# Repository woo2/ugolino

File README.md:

# The Ugolino
An Arduino compaible board based on the ATMEGA328PB that uses the secondary SPI
bus provided by the 328 to interface with 256k of SRAM. There are two aditional
AVRs on borad, both are ATTINY85 microcontrollers. The 85s share the SRAM with
the 328. The 85s' each have four GPIO pins broken out. In order to implement
this functionality, bus switches were used to multiplex the SPI bus and GPIO of
each 85.

An ATMEGA16u2 was used as a USB to serial tranceiver. Right now, support for the
328pb is limited, a patch for the pb is needed for avrdude, and the Arduino IDE
requires an extra board to be installed.

## Known Issues
* ~MISO and MOSI on the Tinys are labeled with respect to the host, where the
tiny is a slave.~(fixed)
* ~SS_328 is not connected to the SS line of the RAM.~ (fixed)
* The PCB does not yet reflect the changes marked fixed.
corrected.

## How to put code on the 328PB

1. Flash the U2:

  Running parts 1 and 2 together did not work for me. It could be that the fuses need to be written before the flash can be programmed properly. Use the same command up to the ```-U``` in part 1 for part 2.
  1. ```sudo avrdude -p m16u2 -c usbtiny -U lfuse:w:0xFF:m -U hfuse:w:0xD9:m -U efuse:w:0xF4:m -U lock:w:0x0F:m -v```
  2. ```flash:w:/home/paul/.arduino15/packages/arduino/hardware/avr/1.6.11/firmwares/atmegaxxu2/arduino-usbserial/Arduino-usbserial-atmega16u2-Uno-Rev3.hex```

2. Right now, the 328pb is not supported by avrdude. To fix this, put
[this](https://savannah.nongnu.org/bugs/?48237) snippet in your
`/etc/avrdude.conf` file. A copy of the fixed file is included. If you trust
me, run `sudo cp avrdude.conf /etc/avrdude.conf` in the root of this repo.

The Ugolino was first created as an intern project while I was working at
[Thimble.io](http://thimble.io), and I have recieved permission to publish this
work publicly.

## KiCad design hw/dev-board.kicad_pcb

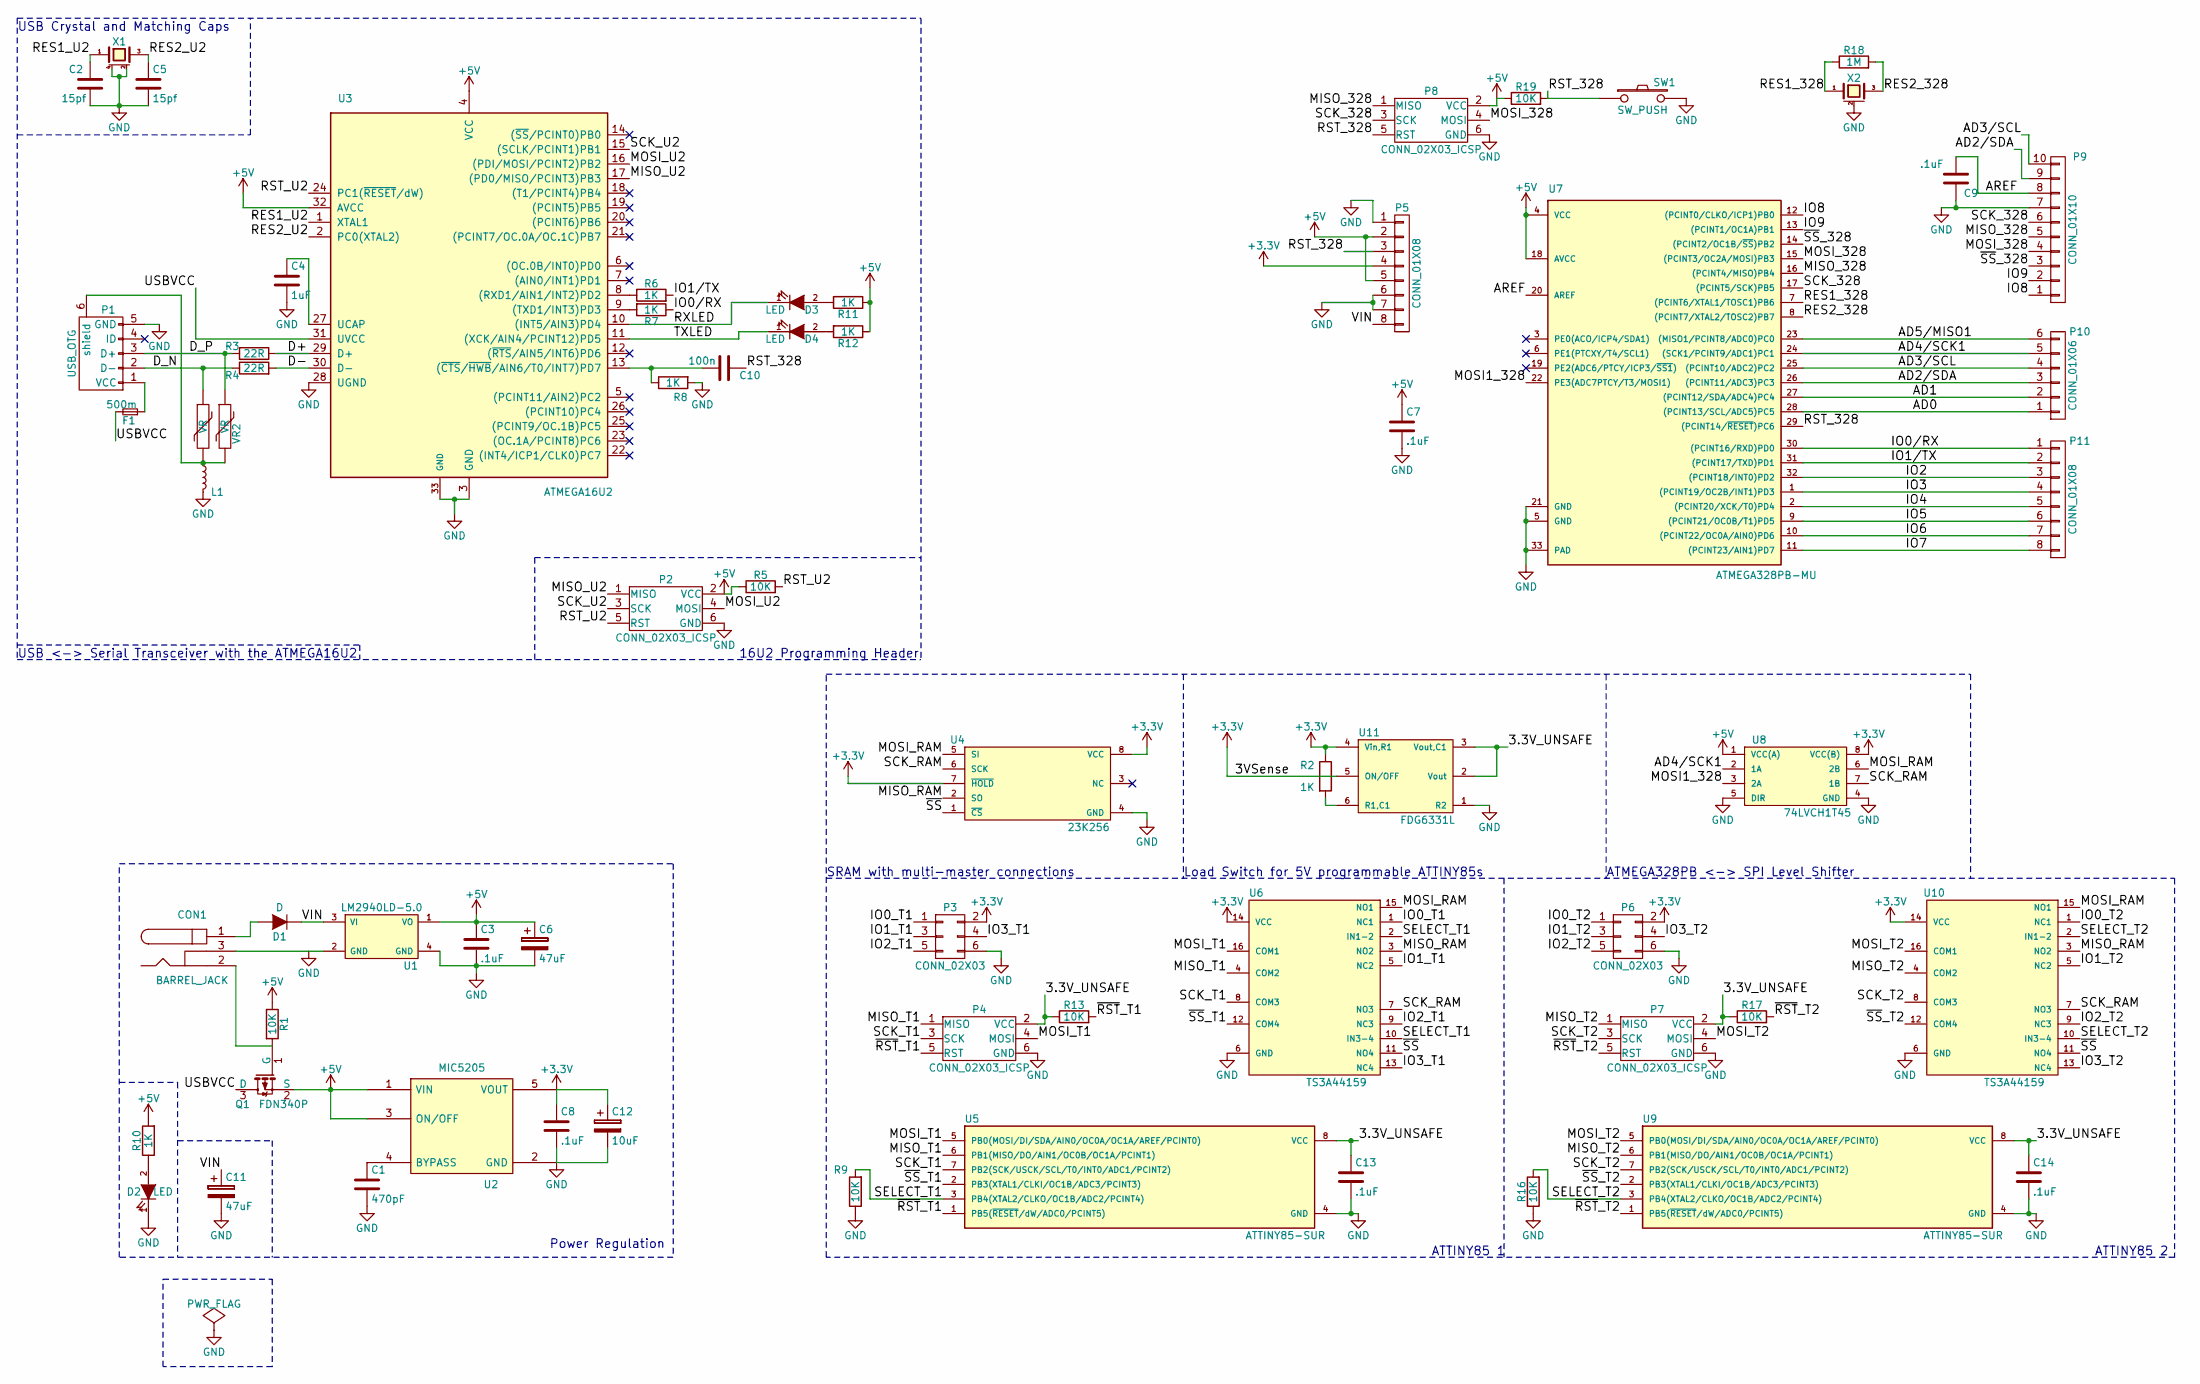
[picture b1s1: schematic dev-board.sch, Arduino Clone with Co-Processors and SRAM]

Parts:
C1: 470pF; C_0603
C2, C5: 15pf; C_0603
C3, C7, C8, C9, C13, C14: .1uF; C_0603
C4: 1uF; C_0603
C6, C11: 47uF; c_elec_5x5.3
C10: 100n; C_0603
C12: 10uF; c_elec_5x5.3
CON1: BARREL_JACK
D1: D; SMD_Diode-1206
D2, D3, D4: LED; LED_0603
F1: 500m; R_1812
L1: Inductor; R_0805
P1: USB_OTG; USB_Micro-B_10118194
P2, P4, P7, P8: CONN_02X03_ICSP; Pin_Header_Straight_2x03_ICSP
P3, P6: CONN_02X03; Pin_Header_Straight_2x03_ATTINY
P5, P11: CONN_01X08; Pin_Header_Straight_1x08
P9: CONN_01X10; Pin_Header_Straight_1x10
P10: CONN_01X06; Pin_Header_Straight_1x06
Q1: FDN340P; SOT-23
R1, R5, R9, R13, R16, R17, R19: 10K; R_0603
R2, R6, R7, R8, R10, R11, R12: 1K; R_0603
R3, R4: 22R; R_0603
R18: 1M; R_0603
SW1: SW_PUSH; PTS645_Button_SMT
U1: LM2940LD-5.0; SOT-223
U2: MIC5205; SOT-23-5
U3: ATMEGA16U2; QFN-32-1EP_5x5mm_Pitch0.5mm
U4: 23K256; SOIC-8-N
U5, U9: ATTINY85-SUR; SOIJ-8_5.3x5.3mm_Pitch1.27mm
U6, U10: TS3A44159; QFN-16-1EP_3x3mm_Pitch0.5mm
U7: ATMEGA328PB-MU; QFN-32-1EP_5x5mm_Pitch0.5mm
U8: 74LVCH1T45; MSOP-8_3x3mm_Pitch0.65mm
U11: FDG6331L; SC-70-6
VR1: VR; R_0603
VR2: VR; R_0603; Part Number CG0603MLC-05E1
X1: CRYSTAL; SMD_Crystal_ABM8G
X2: RESONATOR; AWSCR-CV_Resonator

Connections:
+3V3: C8.1, C12.1, P3.2, P5.4, P6.2, R2.1, U2.5 (VOUT), U4.7 (~HOLD), U4.8 (VCC), U6.14 (VCC), U8.8 (VCC(B)), U10.14 (VCC), U11.4 (Vin,R1), U11.5 (ON/OFF)
+5V: C3.1, C6.1, C7.1, P2.2 (VCC), P5.2, P5.5, P8.2 (VCC), Q1.2 (S), R1.1, R5.1, R10.2, R11.1, R12.1, R19.1, U1.1 (VO), U2.1 (VIN), U2.3 (ON/OFF), U3.4 (VCC), U3.32 (AVCC), U7.4 (VCC), U7.18 (AVCC), U8.1 (VCC(A))
/3.3V_UNSAFE: C13.1, C14.1, P4.2 (VCC), P7.2 (VCC), R13.1, R17.1, U5.8 (VCC), U9.8 (VCC), U11.2 (Vout), U11.3 (Vout,C1)
/AD0: P10.1, U7.28 ((PCINT13/SCL/ADC5)PC5)
/AD1: P10.2, U7.27 ((PCINT12/SDA/ADC4)PC4)
/AD2/SDA: P9.9, P10.3, U7.26 ((PCINT11/ADC3)PC3)
/AD3/SCL: P9.10, P10.4, U7.25 ((PCINT10/ADC2)PC2)
/AD4/SCK1: P10.5, U7.24 ((SCK1/PCINT9/ADC1)PC1), U8.2 (1A)
/AD5/MISO1: P10.6, U7.23 ((MISO1/PCINT8/ADC0)PC0)
/AREF: C9.1, P9.8, U7.20 (AREF)
/D+: R3.1, U3.29 (D+)
/D-: R4.2, U3.30 (D-)
/D_N: P1.2 (D-), R4.1, VR1.1
/D_P: P1.3 (D+), R3.2, VR2.1
/IO0/RX: P11.1, R7.1, U7.30 ((PCINT16/RXD)PD0)
/IO0_T1: P3.1, U6.1 (NC1)
/IO0_T2: P6.1, U10.1 (NC1)
/IO1/TX: P11.2, R6.2, U7.31 ((PCINT17/TXD)PD1)
/IO1_T1: P3.3, U6.5 (NC2)
/IO1_T2: P6.3, U10.5 (NC2)
/IO2: P11.3, U7.32 ((PCINT18/INT0)PD2)
/IO2_T1: P3.5, U6.9 (NC3)
/IO2_T2: P6.5, U10.9 (NC3)
/IO3: P11.4, U7.1 ((PCINT19/OC2B/INT1)PD3)
/IO3_T1: P3.4, U6.13 (NC4)
/IO3_T2: P6.4, U10.13 (NC4)
/IO4: P11.5, U7.2 ((PCINT20/XCK/T0)PD4)
/IO5: P11.6, U7.9 ((PCINT21/OC0B/T1)PD5)
/IO6: P11.7, U7.10 ((PCINT22/OC0A/AIN0)PD6)
/IO7: P11.8, U7.11 ((PCINT23/AIN1)PD7)
/IO8: P9.1, U7.12 ((PCINT0/CLKO/ICP1)PB0)
/IO9: P9.2, U7.13 ((PCINT1/OC1A)PB1)
/MISO_328: P8.1 (MISO), P9.5, U7.16 ((PCINT4/MISO)PB4)
/MISO_RAM: U4.2 (SO), U6.3 (NO2), U10.3 (NO2)
/MISO_T1: P4.1 (MISO), U5.6 (PB1(MISO/DO/AIN1/OC0B/OC1A/PCINT1)), U6.4 (COM2)
/MISO_T2: P7.1 (MISO), U9.6 (PB1(MISO/DO/AIN1/OC0B/OC1A/PCINT1)), U10.4 (COM2)
/MISO_U2: P2.1 (MISO), U3.17 ((PD0/MISO/PCINT3)PB3)
/MOSI1_328: U7.22 (PE3(ADC7PTCY/T3/MOSI1)), U8.3 (2A)
/MOSI_328: P8.4 (MOSI), P9.4, U7.15 ((PCINT3/OC2A/MOSI)PB3)
/MOSI_RAM: U4.5 (SI), U6.15 (NO1), U8.6 (2B), U10.15 (NO1)
/MOSI_T1: P4.4 (MOSI), U5.5 (PB0(MOSI/DI/SDA/AIN0/OC0A/OC1A/AREF/PCI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), U6.16 (COM1)
/MOSI_T2: P7.4 (MOSI), U9.5 (PB0(MOSI/DI/SDA/AIN0/OC0A/OC1A/AREF/PCI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), U10.16 (COM1)
/MOSI_U2: P2.4 (MOSI), U3.16 ((PDI/MOSI/PCINT2)PB2)
/RES1_328: R18.1, U7.7 ((PCINT6/XTAL1/TOSC1)PB6), X2.1
/RES1_U2: C2.1, U3.1 (XTAL1), X1.1
/RES2_328: R18.2, U7.8 ((PCINT7/XTAL2/TOSC2)PB7), X2.3
/RES2_U2: C5.1, U3.2 (PC0(XTAL2)), X1.3
/RST_328: C10.1, P5.3, P8.5 (RST), R19.2, SW1.1, U7.29 ((PCINT14/~RESET~)PC6)
/RST_U2: P2.5 (RST), R5.2, U3.24 (PC1(~RESET~/dW))
/RXLED: D3.1 (K), U3.10 ((INT5/AIN3)PD4)
/SCK_328: P8.3 (SCK), P9.6, U7.17 ((PCINT5/SCK)PB5)
/SCK_RAM: U4.6 (SCK), U6.7 (NO3), U8.7 (1B), U10.7 (NO3)
/SCK_T1: P4.3 (SCK), U5.7 (PB2(SCK/USCK/SCL/T0/INT0/ADC1/PCINT2)), U6.8 (COM3)
/SCK_T2: P7.3 (SCK), U9.7 (PB2(SCK/USCK/SCL/T0/INT0/ADC1/PCINT2)), U10.8 (COM3)
/SCK_U2: P2.3 (SCK), U3.15 ((SCLK/PCINT1)PB1)
/SELECT_T1: R9.2, U5.3 (PB4(XTAL2/CLKO/OC1B/ADC2/PCINT4)), U6.2 (IN1-2), U6.10 (IN3-4)
/SELECT_T2: R16.2, U9.3 (PB4(XTAL2/CLKO/OC1B/ADC2/PCINT4)), U10.2 (IN1-2), U10.10 (IN3-4)
/TXLED: D4.1 (K), U3.11 ((XCK/AIN4/PCINT12)PD5)
/USBVCC: F1.2, Q1.3 (D), U3.31 (UVCC)
/VIN: C11.1, D1.1 (K), P5.8, U1.3 (VI)
/~RST~_T1: P4.5 (RST), R13.2, U5.1 (PB5(~RESET~/dW/ADC0/PCINT5))
/~RST~_T2: P7.5 (RST), R17.2, U9.1 (PB5(~RESET~/dW/ADC0/PCINT5))
/~SS~: U4.1 (~CS), U6.11 (NO4), U10.11 (NO4)
/~SS~_328: P9.3, U7.14 ((PCINT2/OC1B/~SS~)PB2)
/~SS~_T1: U5.2 (PB3(XTAL1/CLKI/OC1B/ADC3/PCINT3)), U6.12 (COM4)
/~SS~_T2: U9.2 (PB3(XTAL1/CLKI/OC1B/ADC3/PCINT3)), U10.12 (COM4)
unnamed: C1.1, U2.4 (BYPASS)
unnamed: C4.1, U3.27 (UCAP)
unnamed: C10.2, R8.1, U3.13 ((~CTS~/~HWB~/AIN6/T0/INT7)PD7)
unnamed: CON1.1, D1.2 (A)
unnamed: CON1.2, Q1.1 (G), R1.2
unnamed: D2.2 (A), R10.1
unnamed: D3.2 (A), R11.2
unnamed: D4.2 (A), R12.2
unnamed: F1.1, P1.1 (VCC)
unnamed: L1.1, P1.6 (shield), VR1.2, VR2.2
unnamed: R2.2, U11.6 (R1,C1)
unnamed: R6.1, U3.8 ((RXD1/AIN1/INT2)PD2)
unnamed: R7.2, U3.9 ((TXD1/INT3)PD3)

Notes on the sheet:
Load Switch for 5V programmable ATTINY85s
SRAM with multi-master connections
ATMEGA328PB <-> SPI Level Shifter
ATTINY85 1
ATTINY85 2
Power Regulation
16U2 Programming Header
USB Crystal and Matching Caps
USB <-> Serial Transceiver with the ATMEGA16U2

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
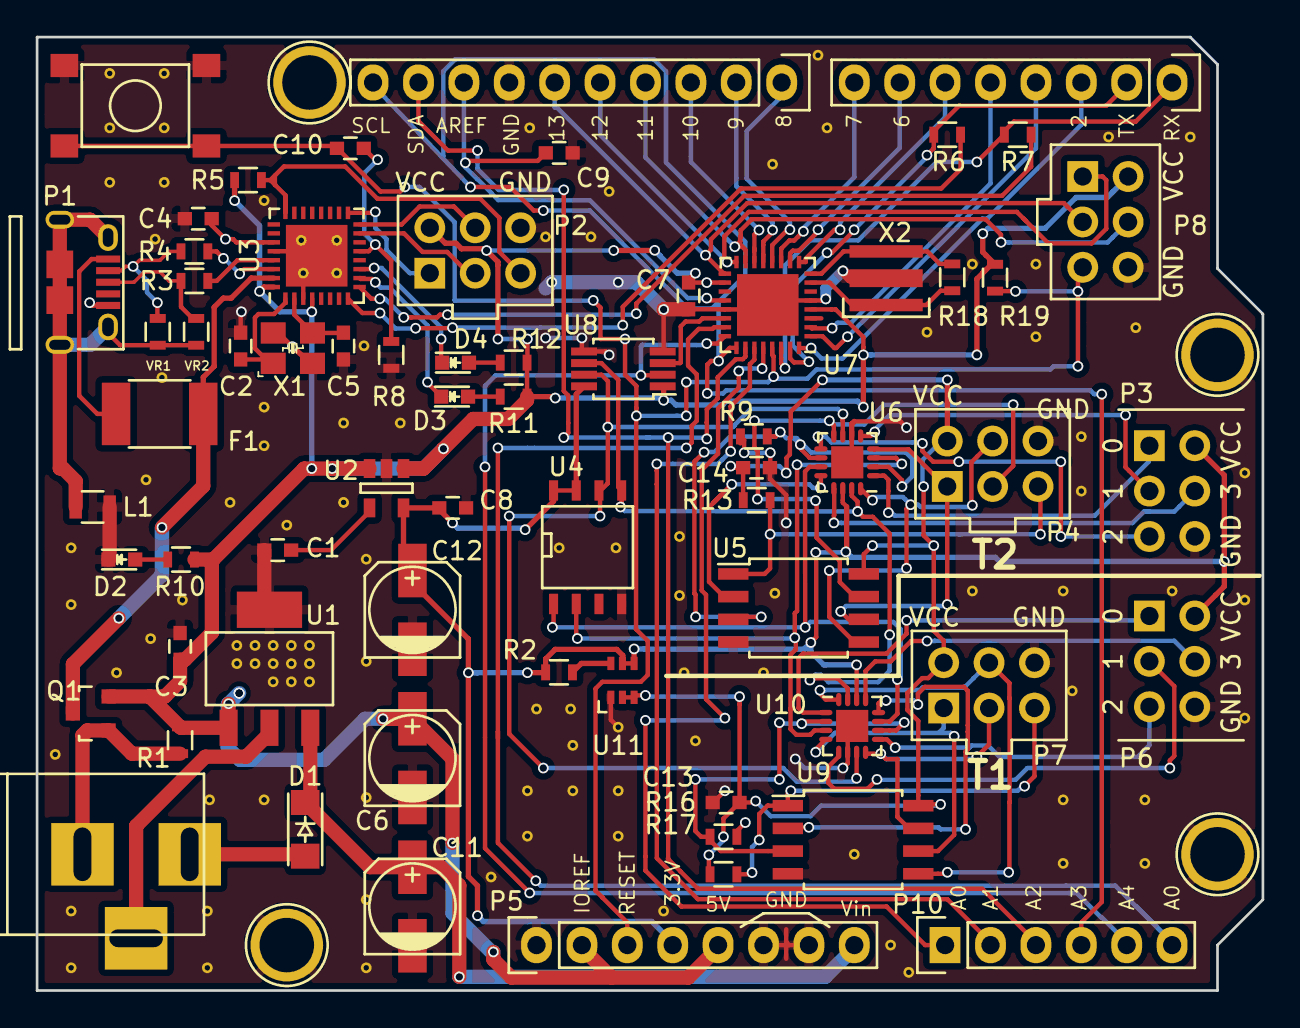
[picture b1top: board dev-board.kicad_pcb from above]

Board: 2 copper layers, 68.6 x 53.3 mm, 70 parts (0 on the bottom side), 81 nets.

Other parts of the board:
P13: CONN_02X03; Arduino_1pin
P14, P22: CONN_02X03_ICSP; Arduino_1pin
P15: CONN_01X08; Arduino_1pin

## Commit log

2016-06-06 Initial kicad commit
2016-06-07 Added U2 and 328. Created ICSP Header with named pins and added gnd pad to 328.
2016-06-07 Complete Header connections and internal U2-328 connections. Power regulation and misc passives are up next.
2016-06-07 Missing regulators. Xtal is fixed. 3.3v done. Power rails organized.
2016-06-08 Add 5V regulator, clean up SOT-223 footprint, created 5V reg schematic symbol
2016-06-08 Add schematic drawing of 328PB
2016-06-08 Added ATTINY85 schematic and SRAM schematic. Added T1's programming header. Up next, T1 needs a bus switch and everything needs to be duplcated for T2.
2016-06-09 Added Bus switch schematic, added a mosfet for power to ram and bs. Needed for programming. BS and ram are not 5v tolerant.
2016-06-09 Switched Safe 3.3v rail for an unsafe rail. This keeps power management less complicated.
2016-06-09 The schematic at this point is complete. Updated todo/readme
2016-06-09 Okay, the Schematic really is done now. Added a level shifter on 328<->SRAM
2016-06-10 Removed opamp and tied 3.3v LDO switch to sense pin on DC connector.
2016-06-10 Completed Footprint assignment.
2016-06-10 Resolved ERC issues. There are three that remain. They are caused by KiCAD not counting passive pins that conect to a power output.
2016-06-13 Add load switch schematic diagram and fix some wiring.
2016-06-13 Fixed added wires to IO ports and added the load switch to the drawing. I'm not 100% certain that the present configuration will work. R1 is not given a value in the DS and there is no explicit ON/OF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
2016-06-13 Label blocked off circuits and section off more areas in schemaic
2016-06-13 PCB is ready for layout
2016-06-13 Coarse placement of power and usb passives. All components are on board. Connectors have the correct footprint. Tinys need better placement. Final adjustments will make placing traces easier.
2016-06-14 Semi-Final PCB layout. Missing R1 for load switch. Pre-traces
2016-06-14 Pre review commit. About 25% routed. Mostly Power.
2016-06-14 The actual pre meeting commit.
2016-06-14 Fix layout.
2016-06-15 No major changes. PCB is 50% routed with clear vert/horiz pattern. This is just a restore point.
2016-06-15 end of day commit
2016-06-16 cleaned up many traces, especially around QFNs and in the power area. Power traces are next.
2016-06-16 add ground plane and stitching vias. All signals routed.
2016-06-16 End of day commit. 12 Unconnected nets. Needs some silikscreen.
2016-06-17 Completed routing.. Macrofab requires a 1.6mm clearance on traces. I made everything with 1.5mm. I'll be back.
2016-06-17 Completed PCB layout.
2016-06-17 Generated Build Files
2016-06-17 Pre-production commit. Silkscreen added and some designators moved away from vias. Added BOM/picknplace
2016-07-08 add 16u2 flashing instructions, rename board files
2016-07-08 clean up readme
2016-07-08 Okay, I think I actually fixed the readme this time. Maybe.
2016-07-08 Not Enough Traling whitespace
2016-07-12 Fix readme
2016-09-28 Add footprint for 4 bit level shifter.
2016-09-28 Add details to readme.
2017-10-02 Fixed typos in readme.
2018-10-15 fixing readme
    typo in "known issues"
    - Happy Monday, ~T
